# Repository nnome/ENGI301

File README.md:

# ENGI301
Repository for ENGI301 course work
git add
git commit -m"Updating README.md"
git push

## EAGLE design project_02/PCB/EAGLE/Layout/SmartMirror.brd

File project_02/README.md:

# PCB Design for Portable Smart Vanity Mirror using EAGLE
## ENGI 301 Course

This repository contains the EAGLE library, schematics, layout, and manufacturing files (Bill of Materials, etc.) required to construct a PCB for a portable, touchscreen smart mirror that allows you to receive weather and news updates for the day.

For more detailed instructions on the motivation for this project, device schematics, and instructions on how to build the device visit: https://www.hackster.io/nome2/portable-smart-vanity-mirror-using-beaglebone-black-9d8d6f

To access the repository with detailed code for the device, visit: https://github.com/nnome/ENGI301/tree/main/project_01

## Instructions

#### To view Project proposal:
1) Click on the 'docs' folder
2) Click on 'ENGI301_project_02_proposal.pptx'

#### To view Assembly Document:
1) Click on the 'docs' folder
4) Click on the 'SmartMirrorAssemblyDocument.pdf'

#### To view Board Layout:
1) Click on the 'PCB' Folder
2) Click on the 'EAGLE' sub-folder
3) Click on the 'Layout' sub-folder
4) Click on the 'SmartMirror.brd'

#### To view Library:
1) Click on the 'PCB' Folder
2) Click on the 'EAGLE' sub-folder
3) Click on the 'Library' sub-folder
4) Click on the 'SmartMirror.lbr'

##### To view Schematics:
1) Click on the 'PCB' Folder
2) Click on the 'EAGLE' sub-folder
3) Click on the 'Schematics' sub-folder
4) Click on the 'SmartMirror.sch'

##### To view Schematics pdf:
1) Click on the 'PCB' Folder
2) Click on the 'EAGLE' sub-folder
3) Click on the 'Schematics' sub-folder
4) Click on the 'SmartMirrorSchematic.pdf'

#### To view Bill of Materials:
1) Click on the 'PCB' Folder
2) Click on the 'EAGLE' sub-folder
3) Click on the 'MFG' (Manufacturing) sub-folder
4) Click on the 'SmartMirror.csv'

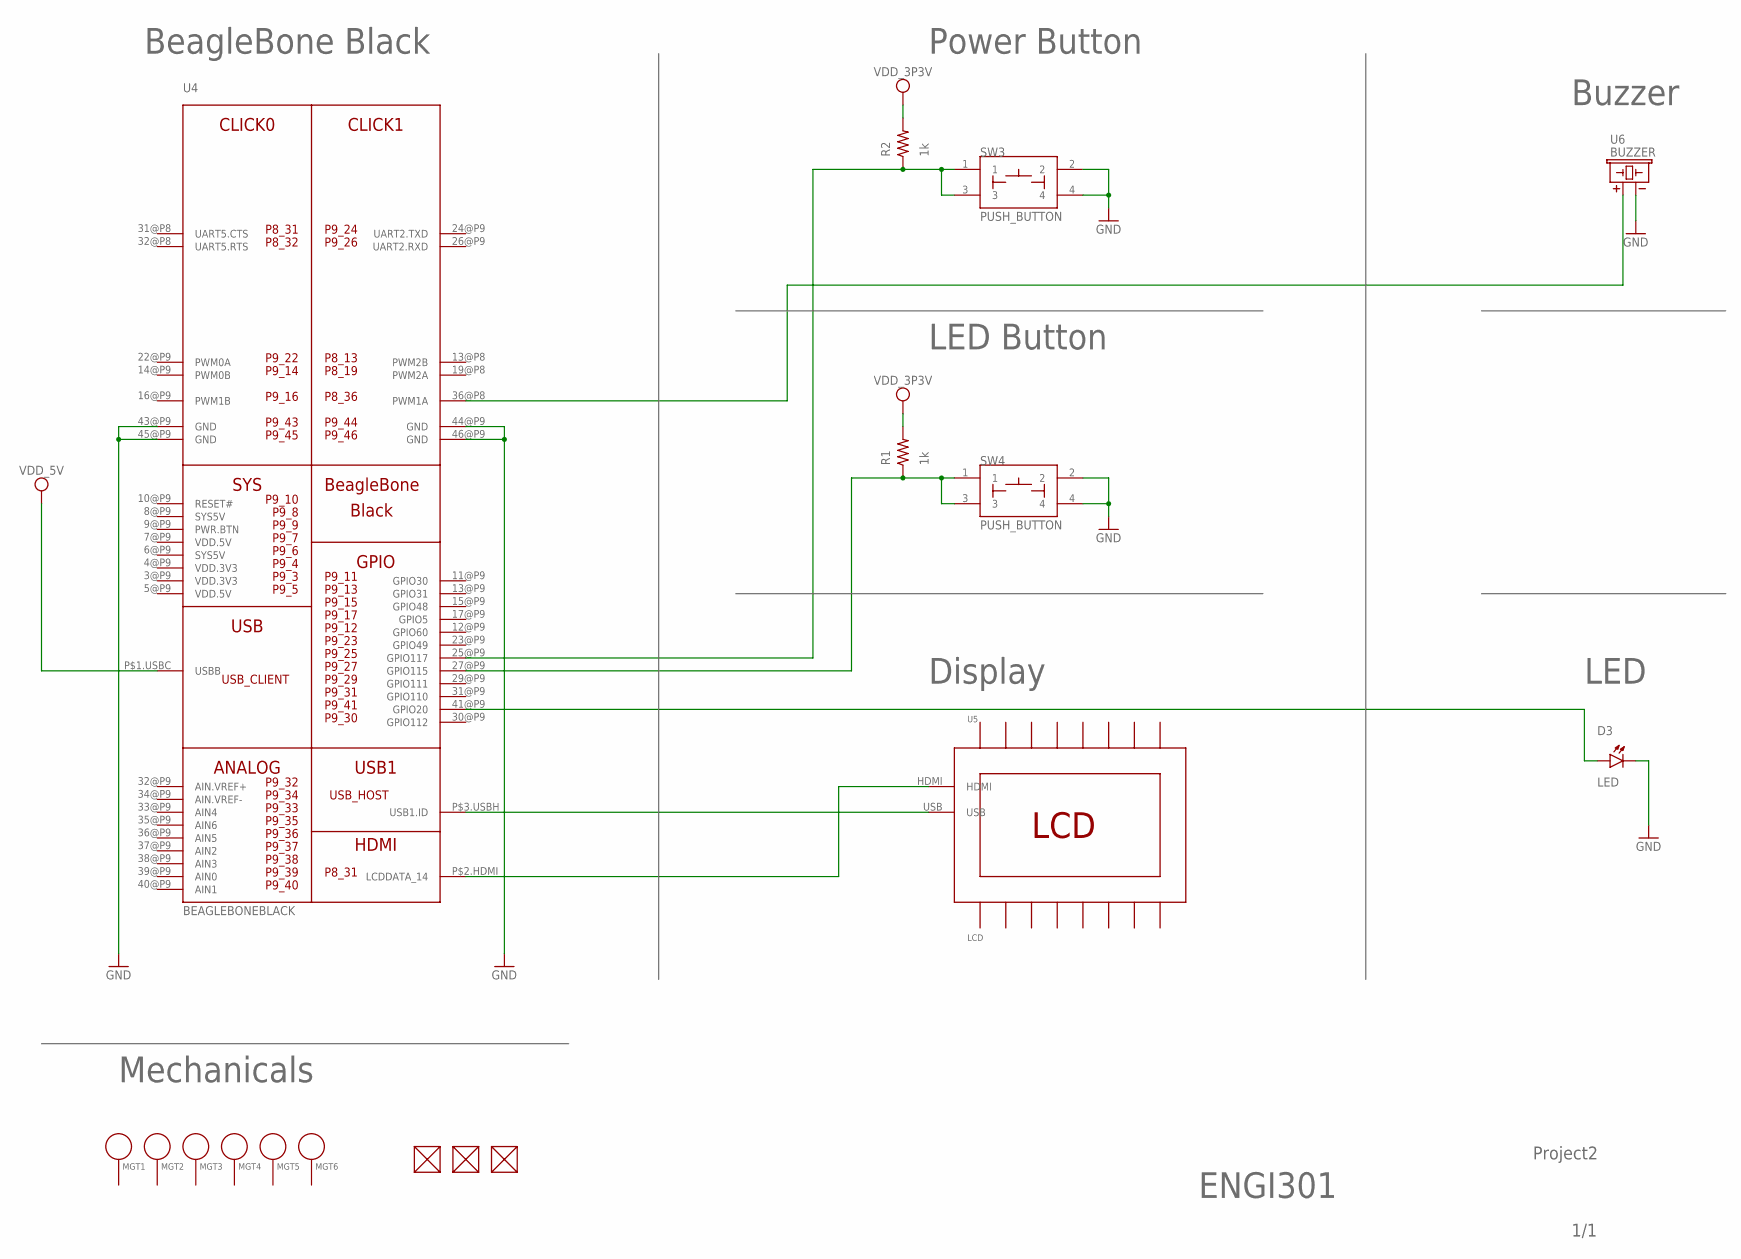
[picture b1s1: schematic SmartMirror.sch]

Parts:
D3: LED; EIA-STD
FUD1, FUD2, FUD3: FIDUCIAL; FIDUCIAL_40MIL
MGT1, MGT2, MGT3, MGT4, MGT5, MGT6: MOUNTING_HOLE
R1, R2: 1k; R0402
SW3, SW4: PUSH_BUTTON; BUTTON_12.5MM
U4: BEAGLEBONEBLACK
U5: LCD
U6: BUZZER; BUZZER_6.5MM

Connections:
GND: D3.CATHODE, SW3.2, SW3.4, SW4.2, SW4.4, U4.43@P9 (GND), U4.44@P9 (GND), U4.45@P9 (GND), U4.46@P9 (GND), U6.-
unnamed: U4.P$2.HDMI (LCDDATA_14), U5.HDMI
unnamed: U4.P$3.USBH (USB1.ID), U5.USB
unnamed: R1.1, SW4.1, SW4.3, U4.27@P9 (GPIO115)
unnamed: U4.36@P8 (PWM1A), U6.+
unnamed: D3.ANODE, U4.41@P9 (GPIO20)
unnamed: R2.1, SW3.1, SW3.3, U4.25@P9 (GPIO117)
SYS5V: U4.6@P9 (SYS5V)
VDD.3V3: U4.3@P9 (VDD.3V3)
VDD_3P3V: R1.2, R2.2
VDD_5V: U4.P$1.USBC (USBB)

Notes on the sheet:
ENGI301
Project2
1/1
BeagleBone Black
Power Button
LED Button
Buzzer
LED
Display
Mechanicals

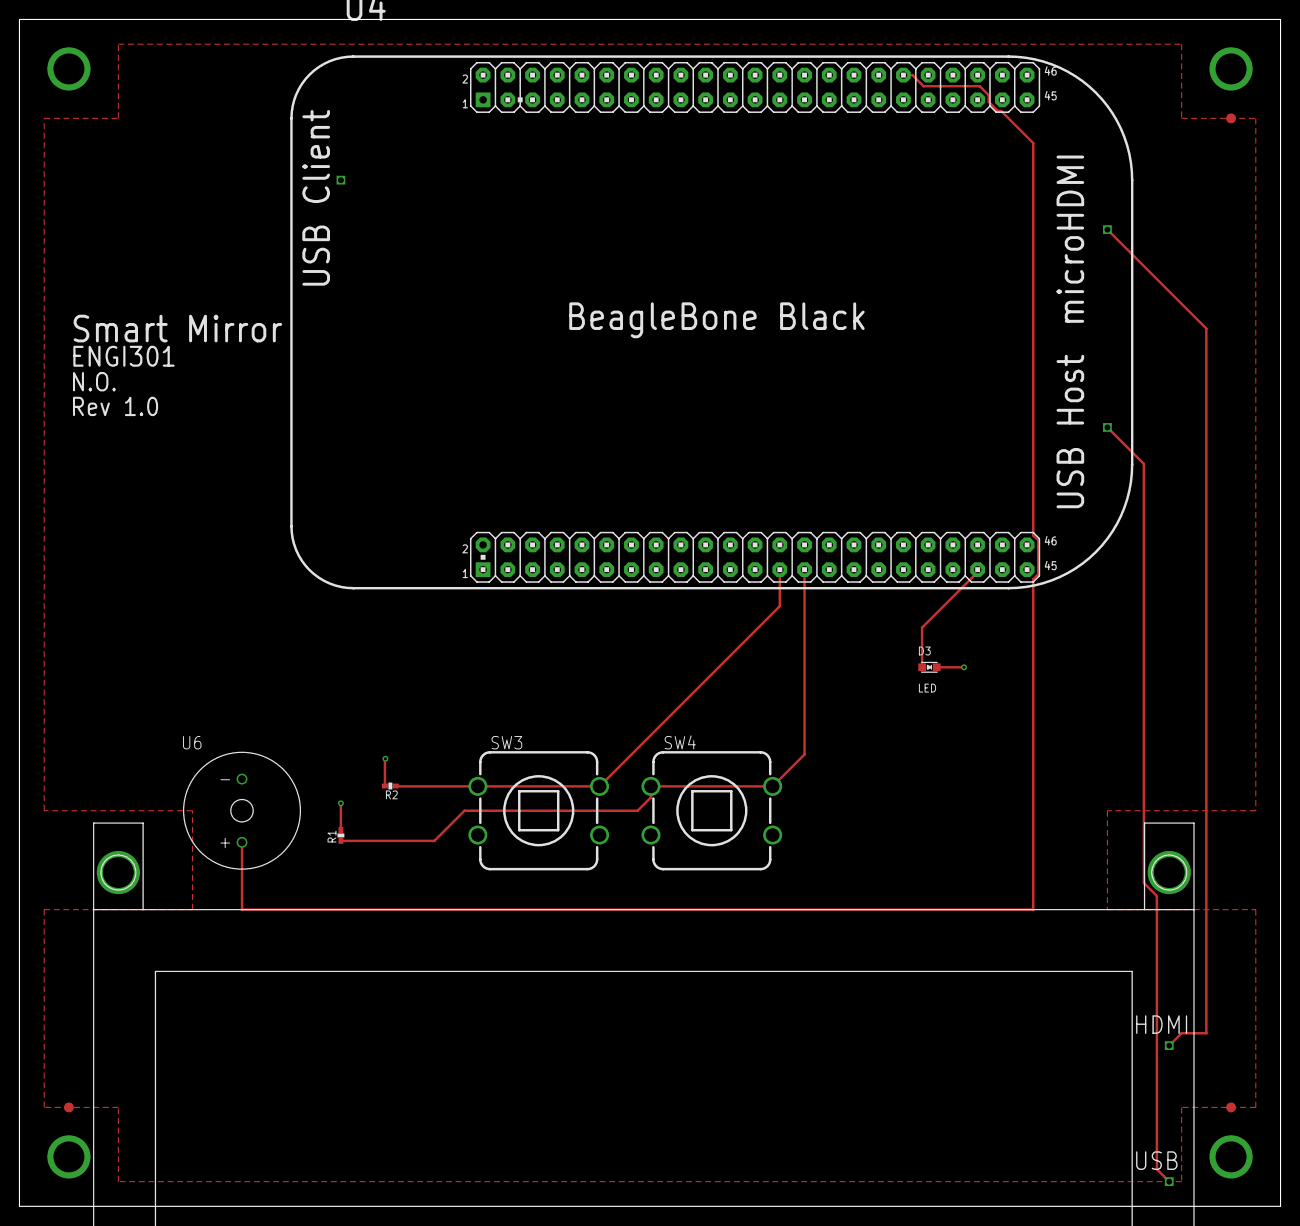
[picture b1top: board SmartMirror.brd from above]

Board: 4 copper layers, 129.5 x 121.9 mm, 17 parts (0 on the bottom side), 8 nets.

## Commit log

2021-09-16 Update README.md
    removed extra text
2021-09-16 adding picture
2021-09-16 removing pictures
2021-10-04 Added Simple Calc Code
2021-10-04 Added blink_led code
2021-10-05 Added comments to code
2021-10-05 Added comments and header to code
2021-10-14 Uploaded Project Proposal
2021-10-14 Create projects and docs files
2021-10-14 Create docs
2021-10-14 Create Ome_ENGI3O1_project_proposal
2021-10-14 Uploaded proposal
2021-11-09 Create RunSmartMirror
    Run script for SmartMirror.py
2021-11-09 Updated Project Proposal
2021-11-09 Format change
2021-11-09 fixed typos
2021-11-09 fix typos
2021-11-17 Upload file
2021-11-17 Create files
2021-11-17 Upload Project Proposal
2021-12-13 Create library
2021-12-15 Add files
2021-12-15 Create file
2021-12-15 Upload library
2021-12-15 Create placeholder
2021-12-15 Upload schematics pdf
2021-12-15 Upload BOM
2021-12-15 Upload board
2021-12-15 Upload schematics
2021-12-15 Upload Assembly Document
2021-12-16 Upload images of top and bottom layers
2021-12-16 Upload Gerber files
2021-12-19 Updated proposal
